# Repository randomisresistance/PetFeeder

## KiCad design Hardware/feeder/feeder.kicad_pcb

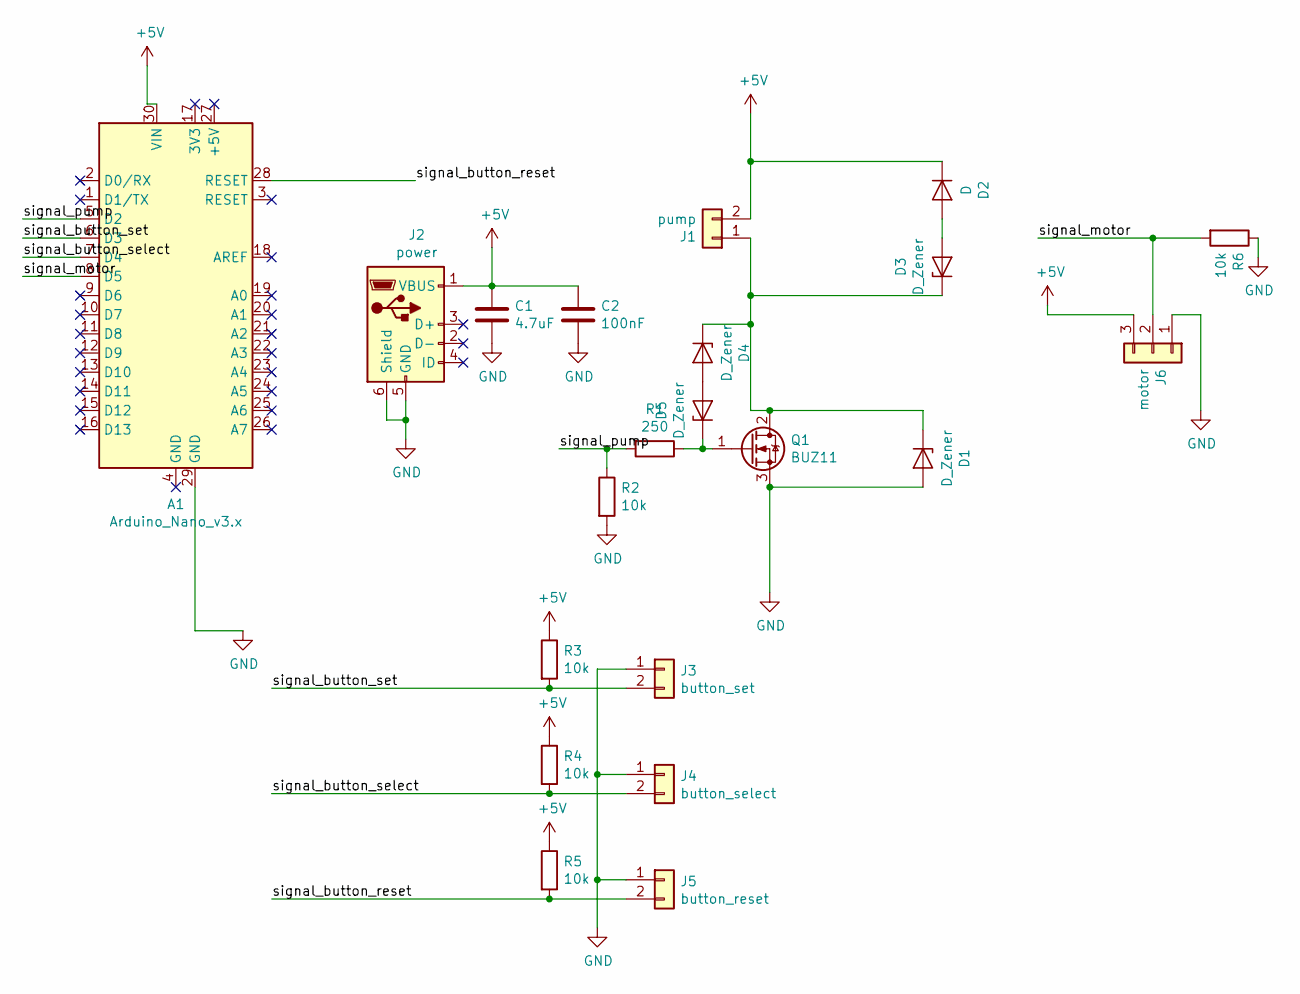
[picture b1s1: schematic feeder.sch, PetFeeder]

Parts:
A1: Arduino_Nano_v3.x; Arduino_Nano
C1: 4.7uF; C_Radial_D4.0mm_H5.0mm_P1.50mm
C2: 100nF; C_Rect_L4.6mm_W3.0mm_P2.50mm_MKS02_FKP02
D1, D3, D4, D5: D_Zener; D_A-405_P7.62mm_Horizontal
D2: D; D_A-405_P7.62mm_Horizontal
J1: pump; PinHeader_1x02_P2.54mm_Horizontal
J2: power; USB_Mini-B_Lumberg_2486_01_Horizontal
J3: button_set; PinHeader_1x02_P2.54mm_Horizontal
J4: button_select; PinHeader_1x02_P2.54mm_Horizontal
J5: button_reset; PinHeader_1x02_P2.54mm_Horizontal
J6: motor; PinHeader_1x03_P2.54mm_Horizontal
Q1: BUZ11; TO-220-3_Horizontal_TabDown
R1: 250; R_Axial_DIN0207_L6.3mm_D2.5mm_P10.16mm_Horizontal
R2, R3, R4, R5, R6: 10k; R_Axial_DIN0207_L6.3mm_D2.5mm_P10.16mm_Horizontal

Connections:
+5V: A1.30 (VIN), C1.1, C2.1, D2.1 (K), J1.2, J2.1 (VBUS), J6.3, R3.1, R4.1, R5.1
/signal_button_reset: A1.28 (RESET), J5.2, R5.2
/signal_button_select: A1.7 (D4), J4.2, R4.2
/signal_button_set: A1.6 (D3), J3.2, R3.2
/signal_motor: A1.8 (D5), J6.2, R6.2
/signal_pump: A1.5 (D2), R1.2, R2.1
GND: A1.29 (GND), C1.2, C2.2, D1.2 (A), J2.5 (GND), J2.6 (Shield), J3.1, J4.1, J5.1, J6.1, Q1.3 (S), R2.2, R6.1
unnamed: D1.1 (K), D3.1 (K), D4.1 (K), J1.1, Q1.2 (D)
unnamed: D2.2 (A), D3.2 (A)
unnamed: D4.2 (A), D5.2 (A)
unnamed: D5.1 (K), Q1.1 (G), R1.1

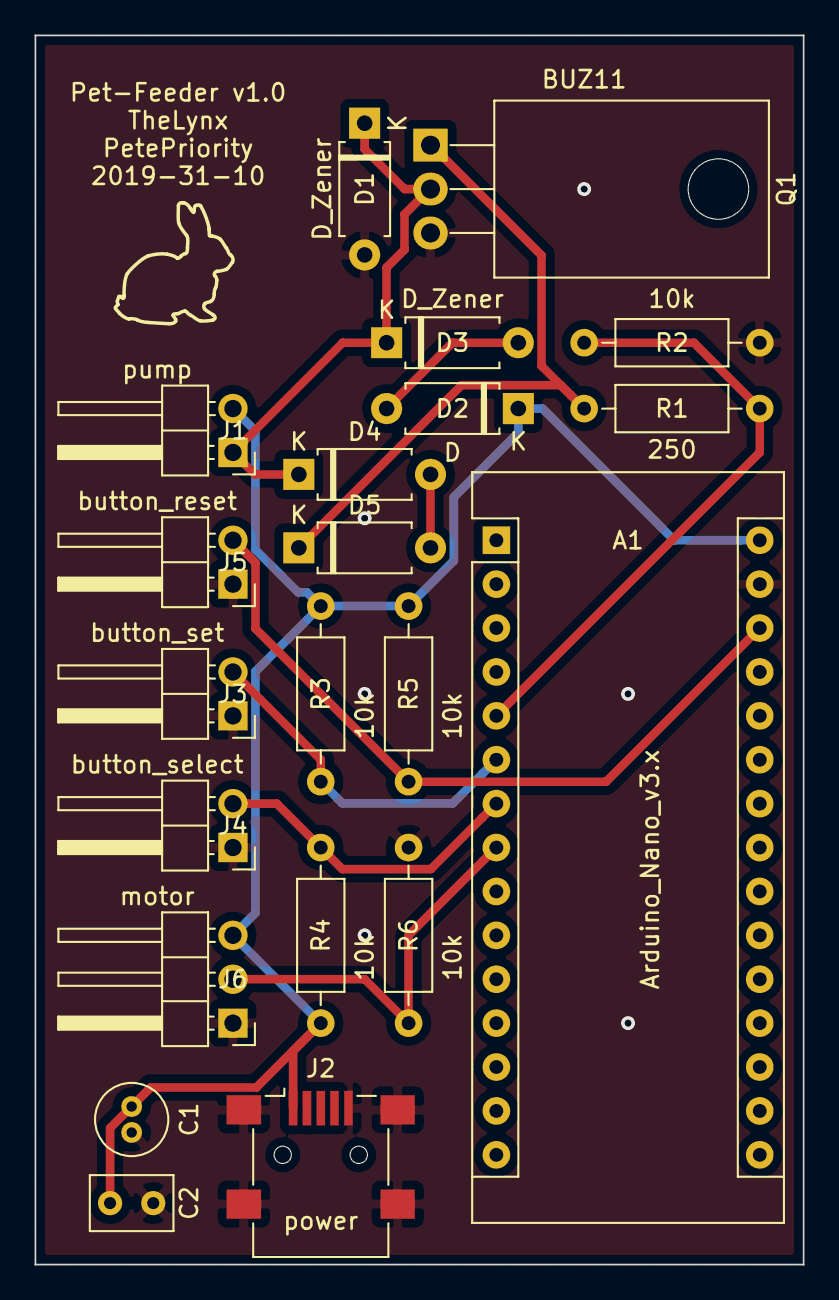
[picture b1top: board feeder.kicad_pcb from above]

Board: 2 copper layers, 44.4 x 71.1 mm, 21 parts (0 on the bottom side), 11 nets.

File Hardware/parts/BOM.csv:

Reference, Quantity, Value, Footprint, Datasheet
A1 ,1,Arduino_Nano_v3.x,Module:Arduino_Nano,http://www.mouser.com/pdfdocs/Gravitech_Arduino_Nano3_0.pdf
D2 ,1,D,Diode_THT:D_A-405_P7.62mm_Horizontal,~
D3 D1 ,2,D_Zener,Diode_THT:D_A-405_P7.62mm_Horizontal,~
J1 ,1,pump,Connector_PinHeader_2.54mm:PinHeader_1x02_P2.54mm_Horizontal,~
J2 ,1,power,Connector_USB:USB_Mini-B_Lumberg_2486_01_Horizontal,~
J3 ,1,button_set,Connector_PinHeader_2.54mm:PinHeader_1x02_P2.54mm_Horizontal,~
J4 ,1,button_select,Connector_PinHeader_2.54mm:PinHeader_1x02_P2.54mm_Horizontal,~
J5 ,1,button_reset,Connector_PinHeader_2.54mm:PinHeader_1x02_P2.54mm_Horizontal,~
J6 ,1,motor,Connector_PinHeader_2.54mm:PinHeader_1x03_P2.54mm_Horizontal,~
Q1 ,1,BUZ11,Package_TO_SOT_THT:TO-220-3_Horizontal_TabDown,http://www.fairchildsemi.com/ds/BU/BUZ11.pdf
R1 ,1,250,Resistor_THT:R_Axial_DIN0207_L6.3mm_D2.5mm_P10.16mm_Horizontal,~
R2 R3 R4 R5 R6 ,5,10k,Resistor_THT:R_Axial_DIN0207_L6.3mm_D2.5mm_P10.16mm_Horizontal,~

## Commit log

2019-10-31 First commit.
2019-10-31 First Steps
2019-10-31 Low-Power lib for Atmel 328P
2019-10-31 Updated hardware schematics and layout
2019-10-31 Updated schematics title and revision date
2019-10-31 Ignore -cache.lib
2019-10-31 Added rabbit svg
2019-10-31 Fix not properly setting clock back to 1MHz
2019-10-31 Toggle motor every second
2019-11-02 some changes in the code
2019-11-02 greater than lower than fuckup
2019-11-02 lower fuckups
2019-11-03 Fix label positions layouts
2019-11-03 Use state machine to setup AmountOfServings
2019-11-04 [WIP] Added some of Benno's improvements
2019-11-04 More of Benno's improvements
    * Increased track width to .5mm
    * Added ground plane on front
    * Placed multiple vias connecting both ground planes across board
    * Minor schematic clean up
2019-11-04 Added capacitors to power supply
2019-11-05 use smaller datatypes
2019-11-05 Change footprints of capacitors
2019-11-05 Add feeder-cache.lib to repo
2019-11-28 Minor changes, new BOM.cvs
2020-10-29 Indent by 4 spaces
2020-10-29 Fix buttons
2020-10-29 Keep powerbank alive by occasionally engaging pump
2020-11-02 Some improvements for the real wordl scenario.
